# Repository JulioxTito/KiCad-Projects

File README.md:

# KiCad Hardware & PCB Design Portfolio
**Julio Tito** | Electrical & Computer Engineering (ECE)  
[GitHub Profile](https://github.com/JulioxTito) • [Master Portfolio & Interview Packet (PDF)](docs/Julio_Tito_Complete_Hardware_Portfolio_Master.pdf) • [Engineering Defense Guide](docs/Interview_Defense_Guide.pdf)

---

## 📌 Overview
This repository serves as a centralized hardware engineering portfolio demonstrating custom Printed Circuit Board (PCB) designs created in **KiCad**. The projects span fundamental analog signal generation, embedded microcontroller robotics systems, and complex 4-layer high-speed digital carrier boards featuring controlled-impedance differential signaling.

Each project showcases both the **3D Raytraced Hardware Model** and the **2D KiCad PCB Designer Layout**, accompanied by production Gerbers, schematics, and design calculations.

---

## 🚀 Featured Hardware Projects

### 1. [Raspberry Pi CM4 High-Speed Carrier Board](01_CM4_HighSpeed_Carrier/)
> **4-Layer High-Speed Digital Carrier** | Broadcom BCM2711, PCIe Gen 2 ($5\text{ Gbps}$) NVMe SSD, Gigabit Ethernet, 4K HDMI, Dual USB 2.0

<p align="center">
  <em>(Left) 3D Raytraced assembly with M.2 NVMe SSD, RJ45 MagJack, and HDMI. (Right) KiCad PCB Editor routing and floorplan.</em>
</p>

* **Stackup**: JLCPCB JLC04161H-7628 ($1.6\text{ mm}$, FR-4 $\epsilon_r \approx 4.6$) with unbroken Layer 2 Ground plane.
* **Controlled Impedance**: PCIe Gen 2 ($100\,\Omega \pm 10\%$, $W=0.20\text{ mm}$, $S=0.18\text{ mm}$) and USB 2.0 ($90\,\Omega \pm 10\%$, $W=0.30\text{ mm}$, $S=0.18\text{ mm}$).
* **Deliverables**: [Project README](01_CM4_HighSpeed_Carrier/) • [Schematics PDF](01_CM4_HighSpeed_Carrier/images/CM4_Schematics.pdf) • [PCB Layout Artwork](01_CM4_HighSpeed_Carrier/images/CM4_PCB_Layout.pdf)

---

### 2. [ESP32-S3 Micromouse Robotics Controller](02_ESP32_Micromouse_Controller/)
> **2-Layer Autonomous Robotics Motherboard** | ESP32-S3 Dual-Core MCU, Dual H-Bridge Motor Drivers, Optical Encoders, IR Sensors

<p align="center">
  <em>(Left) Full-board raytraced 3D isometric perspective. (Right) KiCad PCB Editor layout with ground plane flood.</em>
</p>

* **Core Subsystem**: ESP32-S3-WROOM-1 (240 MHz dual-core Xtensa LX7, Wi-Fi / BLE) with RF antenna keep-out.
* **Peripherals**: Dual H-bridge motor drivers, optical quadrature encoder inputs for closed-loop PID control, dual ToF/IR sensor headers, onboard DC-DC buck power delivery.
* **Deliverables**: [Project README](02_ESP32_Micromouse_Controller/) • [Schematics PDF](02_ESP32_Micromouse_Controller/images/ESP32_Micromouse_Schematic.pdf) • [PCB Layout Artwork](02_ESP32_Micromouse_Controller/images/ESP32_Micromouse_PCB_Layout.pdf)

---

### 3. [LM555 Precision Timer Testboard](03_LM555_Timer_Testboard/)
> **2-Layer Analog & Mixed-Signal Platform** | LM555 Precision Timer, Astable Multivibrator, BJT LED Buffers, Test Points

<p align="center">
  <em>(Left) Raytraced 3D model with floor reflections. (Right) KiCad PCB Editor copper routing & silkscreen.</em>
</p>

* **Circuit Physics**: Astable oscillator with frequency $f = \frac{1.44}{(R_1 + 2R_2)C}$ and low-ESR bypass decoupling.
* **Validation Interface**: High-impedance oscilloscope test points (TRIG, THRES, OUT, VCC, GND) for transient & ripple analysis.
* **Deliverables**: [Project README](03_LM555_Timer_Testboard/) • [Schematics PDF](03_LM555_Timer_Testboard/images/LM555_Timer_Schematic.pdf) • [PCB Layout Artwork](03_LM555_Timer_Testboard/images/LM555_Timer_PCB_Layout.pdf)

---

## 📑 Master Portfolio & Review Deliverables

A compiled 25-page hardware portfolio print packet is available in the [`docs/`](docs/) directory:
* 📄 **[Julio_Tito_Complete_Hardware_Portfolio_Master.pdf](docs/Julio_Tito_Complete_Hardware_Portfolio_Master.pdf)**: Complete 25-page unified master packet containing all schematics, 2D PCB artwork, 3D orthographic renders, and stackup calculations.
* 📄 **[Interview_Defense_Guide.pdf](docs/Interview_Defense_Guide.pdf)**: 1-hour interview walkthrough guide covering architecture trade-offs, IPC-2141 impedance math, PDN decoupling, and DRC verification.

---

## 🛠️ Repository Architecture & Future Expansion

This repository is built modularly so small utility boards, breakout shields, and future complex designs can be dropped in easily:

```text
KiCad-Projects/
├── docs/                                    # Master portfolio PDFs and engineering notes
├── 01_CM4_HighSpeed_Carrier/                # 4-layer high-speed PCIe Gen 2 carrier
│   ├── hardware/                            # KiCad .kicad_pro, .kicad_sch, .kicad_pcb
│   ├── images/                              # 3D renders, PCB layout views, schematics
│   └── README.md                            # High-speed routing rules, stackup, power budget
├── 02_ESP32_Micromouse_Controller/          # Dual H-bridge robotics controller
│   ├── hardware/                            # KiCad files, BOM, production Gerbers
│   ├── images/                              # 3D renders, PCB layout views, schematics
│   └── README.md                            # Motor driver isolation, encoder pinouts
├── 03_LM555_Timer_Testboard/                # Analog precision timing circuit
│   ├── hardware/                            # KiCad files, manufacturing outputs
│   ├── images/                              # 3D renders, PCB layout views, schematics
│   └── README.md                            # Multivibrator formulas, test procedures
└── .gitignore                               # Standard KiCad backup and lock file exclusions
```

---
*Created and maintained by Julio Tito (2026).*

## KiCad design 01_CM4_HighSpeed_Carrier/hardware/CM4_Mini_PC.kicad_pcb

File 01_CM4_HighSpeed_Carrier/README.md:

# Raspberry Pi CM4 High-Speed Carrier Board

<p align="center">
  <em>Figure 1: (Left) High-resolution raytraced 3D render showing M.2 NVMe SSD, RJ45 MagJack, HDMI, and dual Hirose DF40 connectors. (Right) KiCad PCB Editor layout showing component clusters and high-speed routing.</em>
</p>

### 📸 Multi-Angle 3D Hardware Perspectives

<p align="center">
  <em>Figure 2: (Left) Rear isometric perspective showing HDMI port, dual USB ports, and real-time clock. (Right) Low-angle perspective profile highlighting connector stack heights and clearance.</em>
</p>

<p align="center">
  <em>Figure 3: (Left) Orthogonal top assembly layout. (Right) Bottom ground plane flood and power plane distributions.</em>
</p>

---

## 📌 Project Summary
A custom 4-layer carrier board designed for the **Raspberry Pi Compute Module 4 (CM4)**. Engineered for high-speed edge computing, this board integrates a high-performance M.2 NVMe SSD over PCIe Gen 2, Gigabit Ethernet, 4K HDMI display output, dual USB 2.0 ports, a real-time clock (RTC), and a 40-pin GPIO expansion interface.

---

## 📐 Key Specifications
* **Host Processor**: Raspberry Pi Compute Module 4 (Broadcom BCM2711 quad-core Cortex-A72) via dual 100-pin Hirose DF40 high-density connectors.
* **Storage Interface**: M.2 Key-M socket supporting PCIe Gen 2 x1 ($5\text{ Gbps}$) NVMe Solid-State Drives.
* **Networking**: 1000BASE-T Gigabit Ethernet via integrated magnetic RJ45 jack.
* **Display Output**: Full-size HDMI 2.0 connector with integrated ESD protection.
* **Peripherals**: 2x USB 2.0 Type-A ports via onboard USB 2.0 hub; Micro-SD slot for CM4 Lite; RTC battery backup.
* **Board Dimensions**: $85\text{ mm} \times 56\text{ mm}$ (compact credit-card form factor).
* **Layer Count**: 4 Layers (Signal – Ground Reference – Power Split – Signal).

---

## ⚡ High-Speed Controlled Impedance & Stackup
Designed against the **JLCPCB JLC04161H-7628** stackup ($1.6\text{ mm}$ total thickness, FR-4 $\epsilon_r \approx 4.6$):

| Layer | Type | Copper Thickness | Dielectric / Prepreg | Nominal Dielectric Thickness |
| :--- | :--- | :---: | :--- | :---: |
| **Layer 1 (Top)** | High-Speed Signals & Local Power | $35\,\mu\text{m}$ ($1\text{ oz}$) | Prepreg 7628 | $0.21\text{ mm}$ ($8.27\text{ mils}$) |
| **Layer 2 (In1)** | **Unbroken Solid Ground Plane (GND)** | $17.5\,\mu\text{m}$ ($0.5\text{ oz}$) | FR-4 Core | $1.065\text{ mm}$ |
| **Layer 3 (In2)** | **Power Distribution Planes (+3.3V, +5V, +12V)** | $17.5\,\mu\text{m}$ ($0.5\text{ oz}$) | Prepreg 7628 | $0.21\text{ mm}$ ($8.27\text{ mils}$) |
| **Layer 4 (Bottom)**| High-Speed Signals & Low-Speed I/O | $35\,\mu\text{m}$ ($1\text{ oz}$) | — | — |

### Differential Pair Constraints
* **PCIe Gen 2 Differential Pairs** (`PCIE_TX_P/N`, `PCIE_RX_P/N`, `PCIE_CLK_P/N`):
  * Target Differential Impedance: $100\,\Omega \pm 10\%$
  * Trace Width ($W$): $0.20\text{ mm}$ | Gap ($S$): $0.18\text{ mm}$ | Intra-pair Length Mismatch: $<0.15\text{ mm}$ ($6\text{ mils}$)
* **USB 2.0 High-Speed Pairs** (`USB_D_P/N`):
  * Target Differential Impedance: $90\,\Omega \pm 10\%$
  * Trace Width ($W$): $0.30\text{ mm}$ | Gap ($S$): $0.18\text{ mm}$ | Intra-pair Length Mismatch: $<0.50\text{ mm}$

---

## 📁 Project Directory Contents
* [`hardware/`](hardware/): Complete KiCad project database (`CM4_Mini_PC.kicad_pro`), hierarchical schematics, and PCB layout (`CM4_Mini_PC.kicad_pcb`).
* [`images/cm4_3d_render.png`](images/cm4_3d_render.png): High-resolution raytraced 3D rendering.
* [`images/cm4_pcb_layout.jpg`](images/cm4_pcb_layout.jpg): KiCad PCB Editor layout and floorplan screenshot.
* [`images/CM4_PCB_Layout.pdf`](images/CM4_PCB_Layout.pdf): Vector 2D layout artwork showing copper layers and silk.
* [`images/CM4_Schematics.pdf`](images/CM4_Schematics.pdf): 7-sheet hierarchical schematic packet.

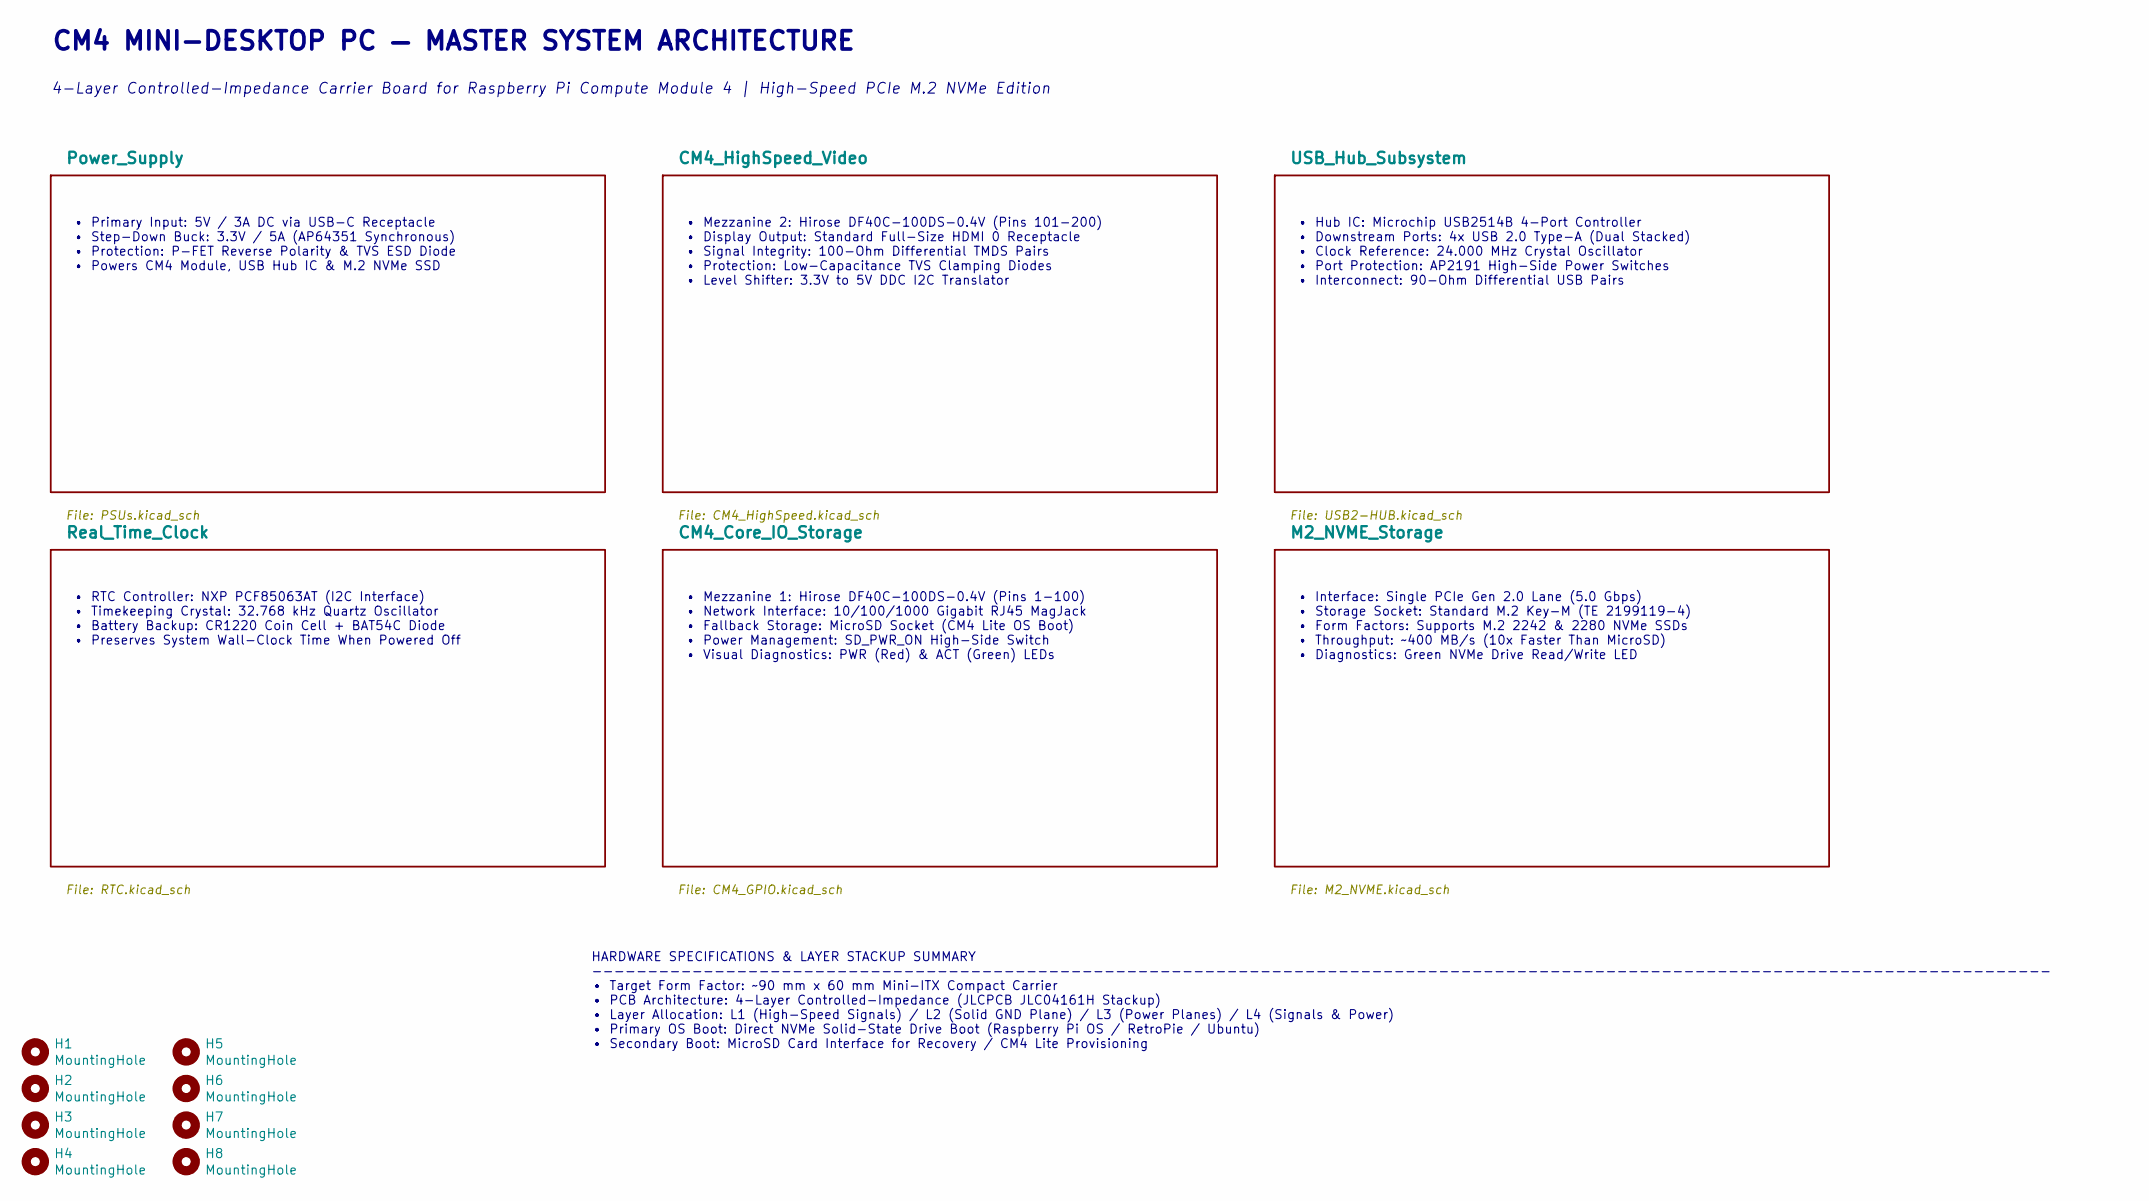
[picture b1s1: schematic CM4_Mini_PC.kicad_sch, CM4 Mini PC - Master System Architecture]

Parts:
H1, H2, H3, H4, H5, H6, H7, H8: MountingHole; MountingHole_2.7mm_M2.5; Part Description M2.5 mounting hole

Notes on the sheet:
CM4 MINI-DESKTOP PC — MASTER SYSTEM ARCHITECTURE
4-Layer Controlled-Impedance Carrier Board for Raspberry Pi Compute Module 4 | High-Speed PCIe M.2 NVMe Edition
• Primary Input: 5V / 3A DC via USB-C Receptacle • Step-Down Buck: 3.3V / 5A (AP64351 Synchronous) • Protection: P-FET Reverse Polarity & TVS ESD Diode • Powers CM4 Module, USB Hub IC & M.2 NVMe SSD
• Mezzanine 2: Hirose DF40C-100DS-0.4V (Pins 101-200) • Display Output: Standard Full-Size HDMI 0 Receptacle • Signal Integrity: 100-Ohm Differential TMDS Pairs • Protection: Low-Capacitance TVS Clamping Diodes • Level Shifter: 3.3V to 5V DDC I2C Translator
• Hub IC: Microchip USB2514B 4-Port Controller • Downstream Ports: 4x USB 2.0 Type-A (Dual Stacked) • Clock Reference: 24.000 MHz Crystal Oscillator • Port Protection: AP2191 High-Side Power Switches • Interconnect: 90-Ohm Differential USB Pairs
• RTC Controller: NXP PCF85063AT (I2C Interface) • Timekeeping Crystal: 32.768 kHz Quartz Oscillator • Battery Backup: CR1220 Coin Cell + BAT54C Diode • Preserves System Wall-Clock Time When Powered Off
• Mezzanine 1: Hirose DF40C-100DS-0.4V (Pins 1-100) • Network Interface: 10/100/1000 Gigabit RJ45 MagJack • Fallback Storage: MicroSD Socket (CM4 Lite OS Boot) • Power Management: SD_PWR_ON High-Side Switch • Visual Diagnostics: PWR (Red) & ACT (Green) LEDs
• Interface: Single PCIe Gen 2.0 Lane (5.0 Gbps) • Storage Socket: Standard M.2 Key-M (TE 2199119-4) • Form Factors: Supports M.2 2242 & 2280 NVMe SSDs • Throughput: ~400 MB/s (10x Faster Than MicroSD) • Diagnostics: Green NVMe Drive Read/Write LED
HARDWARE SPECIFICATIONS & LAYER STACKUP SUMMARY ----------------------------------------------------------------------------------------------------------------------------------- • Target Form Factor: ~90 mm x 60 mm Mini-ITX Compact Carrier • PCB Architecture: 4-Layer Controlled-Impedance (JLCPCB 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

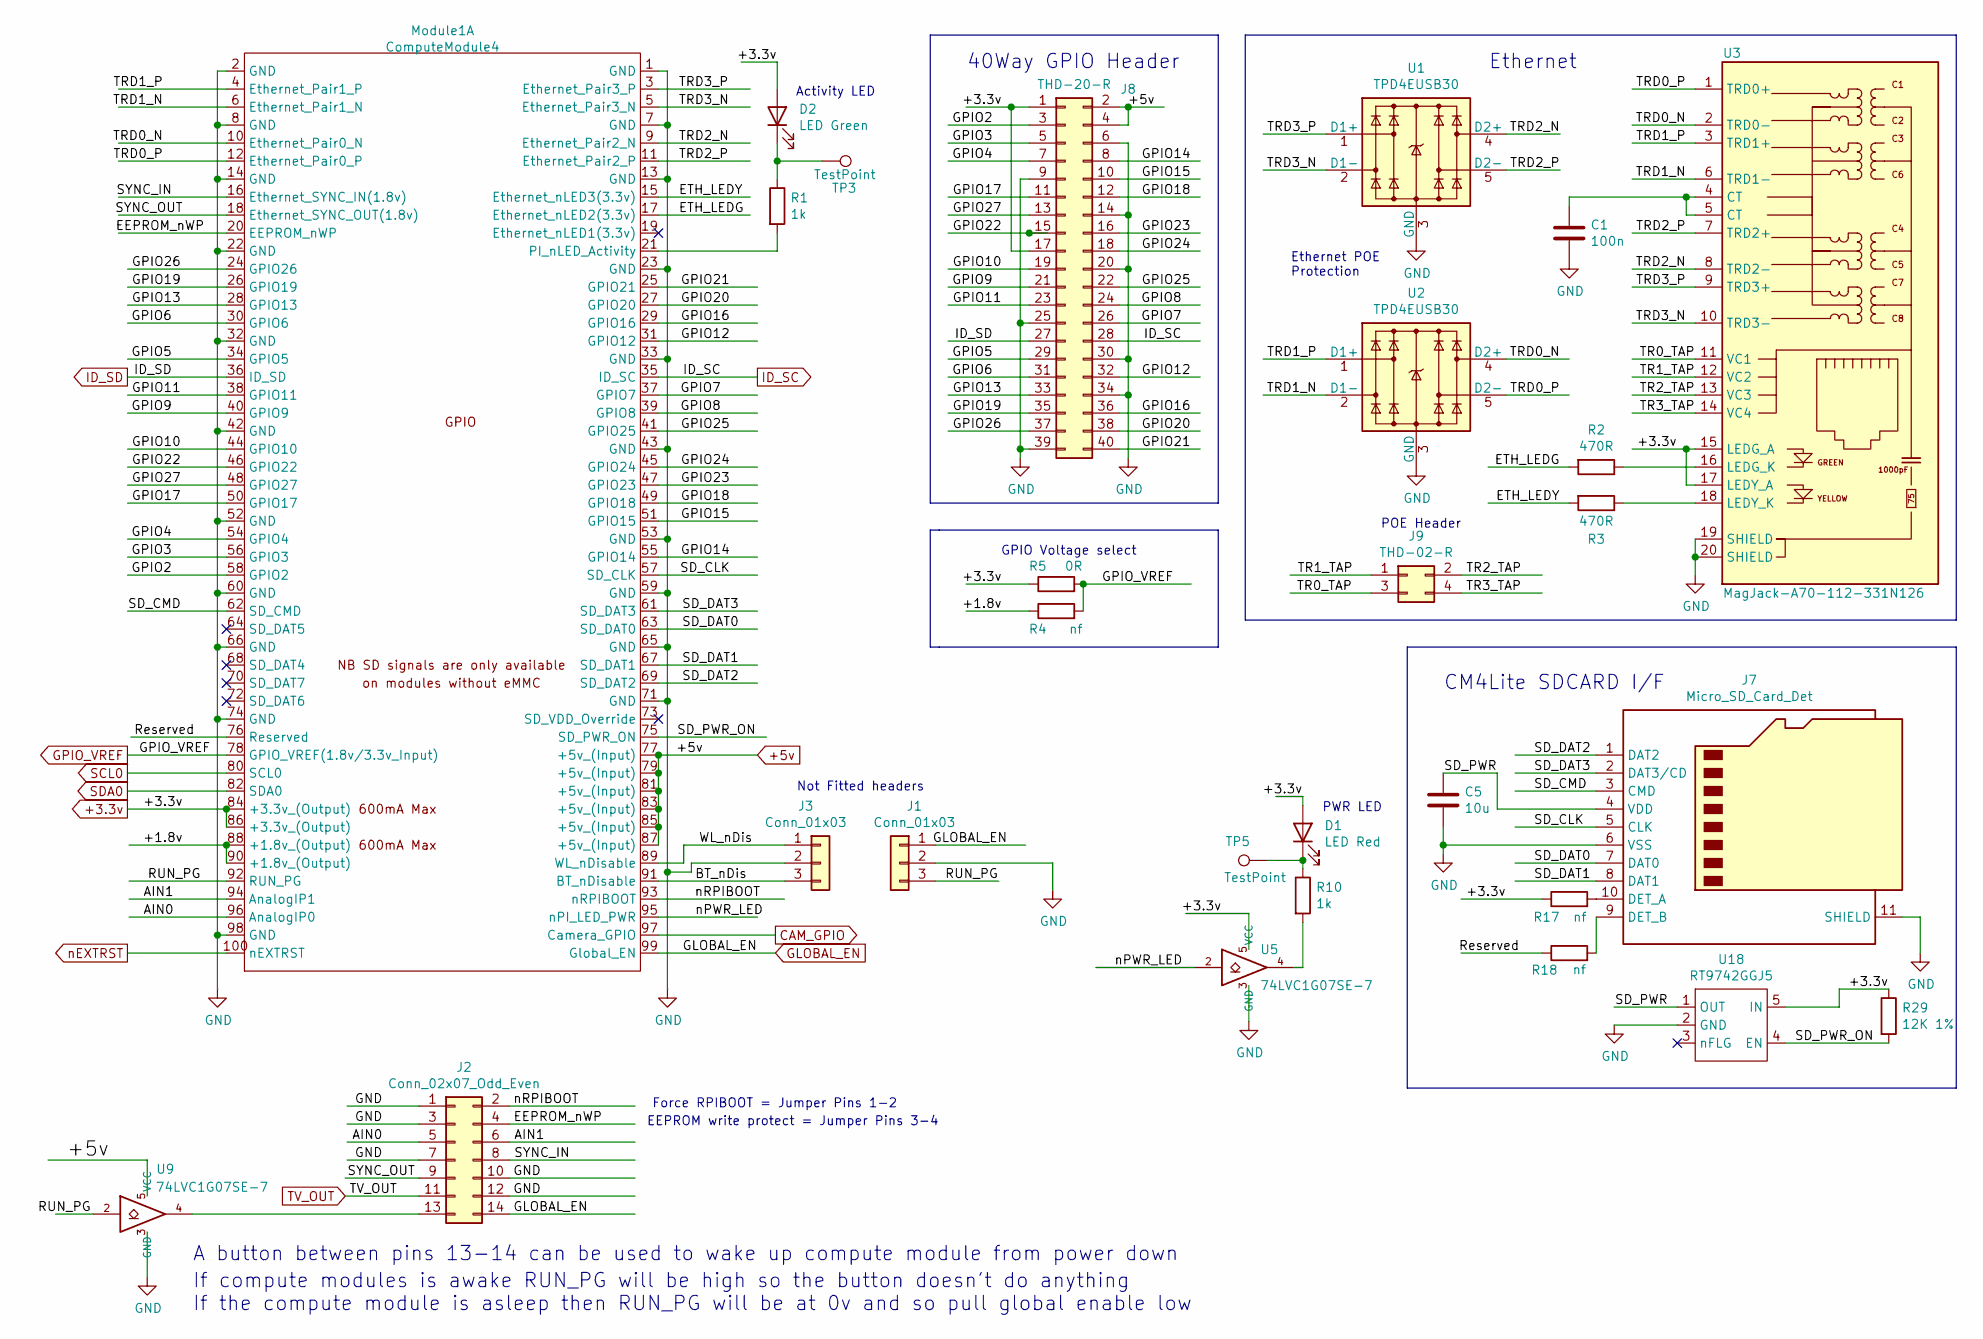
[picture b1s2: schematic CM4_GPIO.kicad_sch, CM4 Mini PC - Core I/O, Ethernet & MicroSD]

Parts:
C1: 100n; C_0402_1005Metric; Part Description 0.1uF 10% 16V Ceramic Capacitor X7R 040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
C5: 10u; C_0805_2012Metric; Part Description 10uF 10% 10V Ceramic Capacitor X7R 0805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
D1: LED Red; LED_0603_1608Metric; Part Description Red 620nm LED Indication - Discrete 2.2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
D2: LED Green; LED_0603_1608Metric; Part Description Green 572nm LED Indication - Discrete 2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
J1, J3: Conn_01x03; PinHeader_1x03_P2.54mm_Vertical; Part Description 3pin 0.1" connector
J2: Conn_02x07_Odd_Even; PinHeader_2x07_P2.54mm_Vertical; Part Description PinHeader_2x07_P2.54mm_Vertical
J7: Micro_SD_Card_Det; SDCARD_MOLEX_503398-1892; Part Description 9 (8 + 1) Position Card Connector micro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
J8: THD-20-R; PinHeader_2x20_P2.54mm_Vertical; Part Description PinHeader_2x20_P2.54mm_Vertical
J9: THD-02-R; PinHeader_2x02_P2.54mm_Vertical; Part Description PinHeader_2x02_P2.54mm_Vertical
Module1: ComputeModule4; Raspberry-Pi-4-Compute-Module; Part Description 100 Position Connector Receptacle, Cent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
R1, R10: 1k; R_0402_1005Metric; Part Description Resistor 1K M1005 1% 63mW
R2, R3: 470R; R_0402_1005Metric; Part Description Resistor 470R M1005 1% 63mW
R4: nf; R_0805_2012Metric_Pad1.20x1.40mm_HandSolder
R5: 0R; R_0805_2012Metric_Pad1.20x1.40mm_HandSolder; Part Description Resistor 0R M2012 5%
R17, R18: nf; R_0402_1005Metric; Part Description Resistor 1K M1005 1% 63mW
R29: 12K 1%; R_0402_1005Metric; Part Description Resistor 12K M1005 1% 63mW
TP3, TP5: TestPoint; TestPoint_Pad_2.0x2.0mm
U1, U2: TPD4EUSB30; USON-10_2.5x1.0mm_P0.5mm; Part Description Quad TVS diode for high speed signals (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
U3: MagJack-A70-112-331N126; TRJG0926HENL; Part Description Gigabit Ethernet Magjack
U5, U9: 74LVC1G07SE-7; SOT-353_SC-70-5; Part Description Buffer, Non-Inverting 1 Element 1 Bit p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
U18: RT9742GGJ5; SOT-23-5; Part Description Power Switch/Driver 1:1 N-Channel 1A TS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

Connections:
+3.3v: D1.2 (A), D2.2 (A), J8.1, J8.17, Module1.84 (+3.3v_(Output)), Module1.86 (+3.3v_(Output)), R5.1, R17.1, R29.1, U3.15 (LEDG_A), U3.17 (LEDY_A), U5.5 (VCC), U18.5 (IN); also elsewhere on the board
+5v: J8.2, J8.4, Module1.77 (+5v_(Input)), Module1.79 (+5v_(Input)), Module1.81 (+5v_(Input)), Module1.83 (+5v_(Input)), Module1.85 (+5v_(Input)), Module1.87 (+5v_(Input)), U9.5 (VCC); also elsewhere on the board
/CM4_Core_IO_Storage/+1.8v: Module1.88 (+1.8v_(Output)), Module1.90 (+1.8v_(Output)), R4.1
/CM4_Core_IO_Storage/AIN0: J2.5, Module1.96 (AnalogIP0)
/CM4_Core_IO_Storage/AIN1: J2.6, Module1.94 (AnalogIP1)
/CM4_Core_IO_Storage/BT_nDis: J3.3, Module1.91 (BT_nDisable)
/CM4_Core_IO_Storage/EEPROM_nWP: J2.4, Module1.20 (EEPROM_nWP)
/CM4_Core_IO_Storage/ETH_LEDG: Module1.17 (Ethernet_nLED2(3.3v)), R2.2
/CM4_Core_IO_Storage/ETH_LEDY: Module1.15 (Ethernet_nLED3(3.3v)), R3.2
/CM4_Core_IO_Storage/GPIO2: J8.3, Module1.58 (GPIO2)
/CM4_Core_IO_Storage/GPIO3: J8.5, Module1.56 (GPIO3)
/CM4_Core_IO_Storage/GPIO4: J8.7, Module1.54 (GPIO4)
/CM4_Core_IO_Storage/GPIO5: J8.29, Module1.34 (GPIO5)
/CM4_Core_IO_Storage/GPIO6: J8.31, Module1.30 (GPIO6)
/CM4_Core_IO_Storage/GPIO7: J8.26, Module1.37 (GPIO7)
/CM4_Core_IO_Storage/GPIO8: J8.24, Module1.39 (GPIO8)
/CM4_Core_IO_Storage/GPIO9: J8.21, Module1.40 (GPIO9)
/CM4_Core_IO_Storage/GPIO10: J8.19, Module1.44 (GPIO10)
/CM4_Core_IO_Storage/GPIO11: J8.23, Module1.38 (GPIO11)
/CM4_Core_IO_Storage/GPIO12: J8.32, Module1.31 (GPIO12)
/CM4_Core_IO_Storage/GPIO13: J8.33, Module1.28 (GPIO13)
/CM4_Core_IO_Storage/GPIO14: J8.8, Module1.55 (GPIO14)
/CM4_Core_IO_Storage/GPIO15: J8.10, Module1.51 (GPIO15)
/CM4_Core_IO_Storage/GPIO16: J8.36, Module1.29 (GPIO16)
/CM4_Core_IO_Storage/GPIO17: J8.11, Module1.50 (GPIO17)
/CM4_Core_IO_Storage/GPIO18: J8.12, Module1.49 (GPIO18)
/CM4_Core_IO_Storage/GPIO19: J8.35, Module1.26 (GPIO19)
/CM4_Core_IO_Storage/GPIO20: J8.38, Module1.27 (GPIO20)
/CM4_Core_IO_Storage/GPIO21: J8.40, Module1.25 (GPIO21)
/CM4_Core_IO_Storage/GPIO22: J8.15, Module1.46 (GPIO22)
/CM4_Core_IO_Storage/GPIO23: J8.16, Module1.47 (GPIO23)
/CM4_Core_IO_Storage/GPIO24: J8.18, Module1.45 (GPIO24)
/CM4_Core_IO_Storage/GPIO25: J8.22, Module1.41 (GPIO25)
/CM4_Core_IO_Storage/GPIO26: J8.37, Module1.24 (GPIO26)
/CM4_Core_IO_Storage/GPIO27: J8.13, Module1.48 (GPIO27)
/CM4_Core_IO_Storage/RUN_PG: J1.3, Module1.92 (RUN_PG), U9.2
/CM4_Core_IO_Storage/Reserved: Module1.76 (Reserved), R18.1
/CM4_Core_IO_Storage/SD_CLK: J7.5 (CLK), Module1.57 (SD_CLK)
/CM4_Core_IO_Storage/SD_CMD: J7.3 (CMD), Module1.62 (SD_CMD)
/CM4_Core_IO_Storage/SD_DAT0: J7.7 (DAT0), Module1.63 (SD_DAT0)
/CM4_Core_IO_Storage/SD_DAT1: J7.8 (DAT1), Module1.67 (SD_DAT1)
/CM4_Core_IO_Storage/SD_DAT2: J7.1 (DAT2), Module1.69 (SD_DAT2)
/CM4_Core_IO_Storage/SD_DAT3: J7.2 (DAT3/CD), Module1.61 (SD_DAT3)
/CM4_Core_IO_Storage/SD_PWR: C5.1, J7.4 (VDD), U18.1 (OUT)
/CM4_Core_IO_Storage/SD_PWR_ON: Module1.75 (SD_PWR_ON), R29.2, U18.4 (EN)
/CM4_Core_IO_Storage/SYNC_IN: J2.8, Module1.16 (Ethernet_SYNC_IN(1.8v))
/CM4_Core_IO_Storage/SYNC_OUT: J2.9, Module1.18 (Ethernet_SYNC_OUT(1.8v))
/CM4_Core_IO_Storage/TR0_TAP: J9.3, U3.11 (VC1)
/CM4_Core_IO_Storage/TR1_TAP: J9.1, U3.12 (VC2)
/CM4_Core_IO_Storage/TR2_TAP: J9.2, U3.13 (VC3)
/CM4_Core_IO_Storage/TR3_TAP: J9.4, U3.14 (VC4)
/CM4_Core_IO_Storage/TRD0_N: Module1.10 (Ethernet_Pair0_N), U2.4 (D2+), U2.7, U3.2 (TRD0-)
/CM4_Core_IO_Storage/TRD0_P: Module1.12 (Ethernet_Pair0_P), U2.5 (D2-), U2.6, U3.1 (TRD0+)
/CM4_Core_IO_Storage/TRD1_N: Module1.6 (Ethernet_Pair1_N), U2.2 (D1-), U2.9, U3.6 (TRD1-)
/CM4_Core_IO_Storage/TRD1_P: Module1.4 (Ethernet_Pair1_P), U2.1 (D1+), U2.10, U3.3 (TRD1+)
/CM4_Core_IO_Storage/TRD2_N: Module1.9 (Ethernet_Pair2_N), U1.4 (D2+), U1.7, U3.8 (TRD2-)
/CM4_Core_IO_Storage/TRD2_P: Module1.11 (Ethernet_Pair2_P), U1.5 (D2-), U1.6, U3.7 (TRD2+)
/CM4_Core_IO_Storage/TRD3_N: Module1.5 (Ethernet_Pair3_N), U1.2 (D1-), U1.9, U3.10 (TRD3-)
/CM4_Core_IO_Storage/TRD3_P: Module1.3 (Ethernet_Pair3_P), U1.1 (D1+), U1.10, U3.9 (TRD3+)
/CM4_Core_IO_Storage/WL_nDis: J3.1, Module1.89 (WL_nDisable)
/CM4_Core_IO_Storage/nPWR_LED: Module1.95 (nPI_LED_PWR), U5.2
/CM4_Core_IO_Storage/nRPIBOOT: J2.2, Module1.93 (nRPIBOOT)
CAM_GPIO: Module1.97 (Camera_GPIO); also elsewhere on the board
GLOBAL_EN: J1.1, J2.14, Module1.99 (Global_EN); also elsewhere on the board
GND: C1.2, C5.2, J1.2, J2.1, J2.3, J2.7, J2.10, J2.12, J3.2, J7.6 (VSS), J7.11 (SHIELD), J8.6, J8.9, J8.14, J8.20, J8.25, J8.30, J8.34, J8.39, Module1.1 (GND), Module1.2 (GND), Module1.7 (GND), Module1.8 (GND), Module1.13 (GND), Module1.14 (GND), Module1.22 (GND), Module1.23 (GND), Module1.32 (GND), Module1.33 (GND), Module1.42 (GND), Module1.43 (GND), Module1.52 (GND), Module1.53 (GND), Module1.59 (GND), Module1.60 (GND), Module1.65 (GND), Module1.66 (GND), Module1.71 (GND), Module1.74 (GND), Module1.98 (GND), U1.3 (GND), U1.8 (GND), U2.3 (GND), U2.8 (GND), U3.19 (SHIELD), U3.20 (SHIELD), U5.3 (GND), U9.3 (GND), U18.2 (GND); also elsewhere on the board
GPIO_VREF: Module1.78 (GPIO_VREF(1.8v/3.3v_Input)), R4.2, R5.2; also elsewhere on the board
ID_SC: J8.28, Module1.35 (ID_SC)
ID_SD: J8.27, Module1.36 (ID_SD)
unnamed: C1.1, U3.4 (CT), U3.5 (CT)
unnamed: D1.1 (K), R10.1, TP5.1 (1_1)
unnamed: D2.1 (K), R1.1, TP3.1 (1_1)
unnamed: J2.13, U9.4
unnamed: J7.10 (DET_A), R17.2
unnamed: J7.9 (DET_B), R18.2
unnamed: Module1.21 (PI_nLED_Activity), R1.2
unnamed: R10.2, U5.4
unnamed: R2.1, U3.16 (LEDG_K)
unnamed: R3.1, U3.18 (LEDY_K)
SCL0: Module1.80 (SCL0); also elsewhere on the board
SDA0: Module1.82 (SDA0); also elsewhere on the board
TV_OUT: J2.11; also elsewhere on the board
nEXTRST: Module1.100 (nEXTRST); also elsewhere on the board

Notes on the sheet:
PWR LED
Ethernet POE Protection
40Way GPIO Header
CM4Lite SDCARD I/F
GPIO Voltage select
Ethernet
Activity LED
EEPROM write protect = Jumper Pins 3-4
Not Fitted headers
A button between pins 13-14 can be used to wake up compute module from power down
If compute modules is awake RUN_PG will be high so the button doesn't do anything If the compute module is asleep then RUN_PG will be at 0v and so pull global enable low
Force RPIBOOT = Jumper Pins 1-2
POE Header

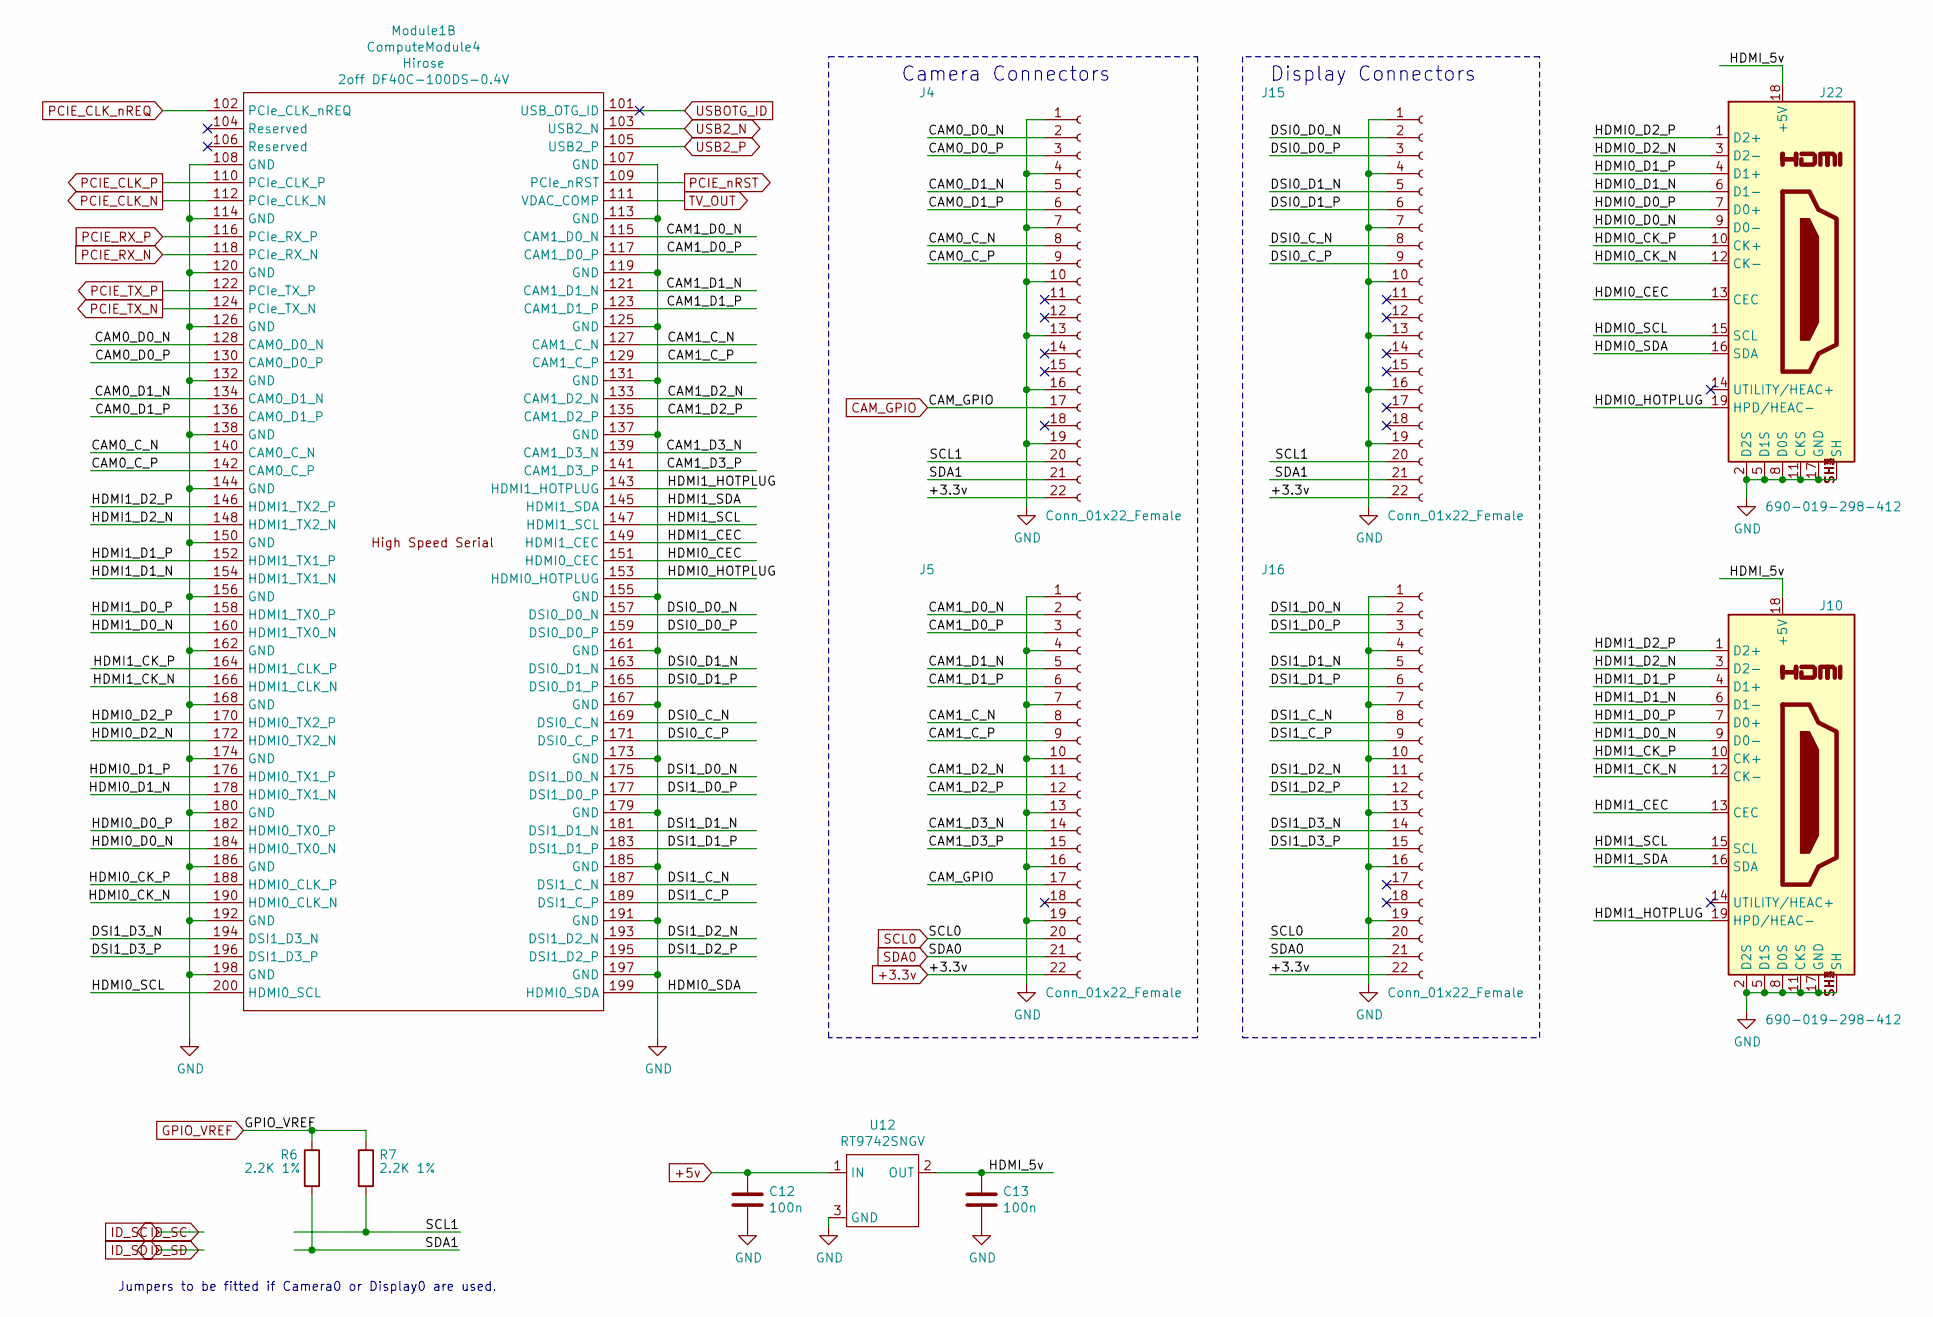
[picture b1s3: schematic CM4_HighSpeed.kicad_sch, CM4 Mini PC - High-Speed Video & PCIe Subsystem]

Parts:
C12, C13: 100n; C_0402_1005Metric; Part Description 0.1uF 10% 16V Ceramic Capacitor X7R 040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
J4, J5, J15, J16: Conn_01x22_Female; Hirose_FH12-22S-0.5SH_1x22-1MP_P0.50mm_Horizontal; Part Description 22 Position FFC, FPC Connector Contacts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
J10, J22: 690-019-298-412; EDAC 690-019-298-412; Part Description HDMI Connector, Right Angle, 19 Contact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
Module1: ComputeModule4; Raspberry-Pi-4-Compute-Module; Part Description 100 Position Connector Receptacle, Cent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
R6, R7: 2.2K 1%; R_0402_1005Metric; Part Description Resistor 2.2K M1005 1% 63mW
U12: RT9742SNGV; SOT-23; Part Description Power Switch/Driver 1:1 N-Channel 500mA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

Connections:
+3.3v: J4.22, J5.22, J15.22, J16.22; also elsewhere on the board
+5v: C12.1, U12.1 (IN); also elsewhere on the board
/CM4_HighSpeed_Video/CAM0_C_N: J4.8, Module1.140 (CAM0_C_N)
/CM4_HighSpeed_Video/CAM0_C_P: J4.9, Module1.142 (CAM0_C_P)
/CM4_HighSpeed_Video/CAM0_D0_N: J4.2, Module1.128 (CAM0_D0_N)
/CM4_HighSpeed_Video/CAM0_D0_P: J4.3, Module1.130 (CAM0_D0_P)
/CM4_HighSpeed_Video/CAM0_D1_N: J4.5, Module1.134 (CAM0_D1_N)
/CM4_HighSpeed_Video/CAM0_D1_P: J4.6, Module1.136 (CAM0_D1_P)
/CM4_HighSpeed_Video/CAM1_C_N: J5.8, Module1.127 (CAM1_C_N)
/CM4_HighSpeed_Video/CAM1_C_P: J5.9, Module1.129 (CAM1_C_P)
/CM4_HighSpeed_Video/CAM1_D0_N: J5.2, Module1.115 (CAM1_D0_N)
/CM4_HighSpeed_Video/CAM1_D0_P: J5.3, Module1.117 (CAM1_D0_P)
/CM4_HighSpeed_Video/CAM1_D1_N: J5.5, Module1.121 (CAM1_D1_N)
/CM4_HighSpeed_Video/CAM1_D1_P: J5.6, Module1.123 (CAM1_D1_P)
/CM4_HighSpeed_Video/CAM1_D2_N: J5.11, Module1.133 (CAM1_D2_N)
/CM4_HighSpeed_Video/CAM1_D2_P: J5.12, Module1.135 (CAM1_D2_P)
/CM4_HighSpeed_Video/CAM1_D3_N: J5.14, Module1.139 (CAM1_D3_N)
/CM4_HighSpeed_Video/CAM1_D3_P: J5.15, Module1.141 (CAM1_D3_P)
/CM4_HighSpeed_Video/DSI0_C_N: J15.8, Module1.169 (DSI0_C_N)
/CM4_HighSpeed_Video/DSI0_C_P: J15.9, Module1.171 (DSI0_C_P)
/CM4_HighSpeed_Video/DSI0_D0_N: J15.2, Module1.157 (DSI0_D0_N)
/CM4_HighSpeed_Video/DSI0_D0_P: J15.3, Module1.159 (DSI0_D0_P)
/CM4_HighSpeed_Video/DSI0_D1_N: J15.5, Module1.163 (DSI0_D1_N)
/CM4_HighSpeed_Video/DSI0_D1_P: J15.6, Module1.165 (DSI0_D1_P)
/CM4_HighSpeed_Video/DSI1_C_N: J16.8, Module1.187 (DSI1_C_N)
/CM4_HighSpeed_Video/DSI1_C_P: J16.9, Module1.189 (DSI1_C_P)
/CM4_HighSpeed_Video/DSI1_D0_N: J16.2, Module1.175 (DSI1_D0_N)
/CM4_HighSpeed_Video/DSI1_D0_P: J16.3, Module1.177 (DSI1_D0_P)
/CM4_HighSpeed_Video/DSI1_D1_N: J16.5, Module1.181 (DSI1_D1_N)
/CM4_HighSpeed_Video/DSI1_D1_P: J16.6, Module1.183 (DSI1_D1_P)
/CM4_HighSpeed_Video/DSI1_D2_N: J16.11, Module1.193 (DSI1_D2_N)
/CM4_HighSpeed_Video/DSI1_D2_P: J16.12, Module1.195 (DSI1_D2_P)
/CM4_HighSpeed_Video/DSI1_D3_N: J16.14, Module1.194 (DSI1_D3_N)
/CM4_HighSpeed_Video/DSI1_D3_P: J16.15, Module1.196 (DSI1_D3_P)
/CM4_HighSpeed_Video/HDMI0_CEC: J22.13 (CEC), Module1.151 (HDMI0_CEC)
/CM4_HighSpeed_Video/HDMI0_CK_N: J22.12 (CK-), Module1.190 (HDMI0_CLK_N)
/CM4_HighSpeed_Video/HDMI0_CK_P: J22.10 (CK+), Module1.188 (HDMI0_CLK_P)
/CM4_HighSpeed_Video/HDMI0_D0_N: J22.9 (D0-), Module1.184 (HDMI0_TX0_N)
/CM4_HighSpeed_Video/HDMI0_D0_P: J22.7 (D0+), Module1.182 (HDMI0_TX0_P)
/CM4_HighSpeed_Video/HDMI0_D1_N: J22.6 (D1-), Module1.178 (HDMI0_TX1_N)
/CM4_HighSpeed_Video/HDMI0_D1_P: J22.4 (D1+), Module1.176 (HDMI0_TX1_P)
/CM4_HighSpeed_Video/HDMI0_D2_N: J22.3 (D2-), Module1.172 (HDMI0_TX2_N)
/CM4_HighSpeed_Video/HDMI0_D2_P: J22.1 (D2+), Module1.170 (HDMI0_TX2_P)
/CM4_HighSpeed_Video/HDMI0_HOTPLUG: J22.19 (HPD/HEAC-), Module1.153 (HDMI0_HOTPLUG)
/CM4_HighSpeed_Video/HDMI0_SCL: J22.15 (SCL), Module1.200 (HDMI0_SCL)
/CM4_HighSpeed_Video/HDMI0_SDA: J22.16 (SDA), Module1.199 (HDMI0_SDA)
/CM4_HighSpeed_Video/HDMI1_CEC: J10.13 (CEC), Module1.149 (HDMI1_CEC)
/CM4_HighSpeed_Video/HDMI1_CK_N: J10.12 (CK-), Module1.166 (HDMI1_CLK_N)
/CM4_HighSpeed_Video/HDMI1_CK_P: J10.10 (CK+), Module1.164 (HDMI1_CLK_P)
/CM4_HighSpeed_Video/HDMI1_D0_N: J10.9 (D0-), Module1.160 (HDMI1_TX0_N)
/CM4_HighSpeed_Video/HDMI1_D0_P: J10.7 (D0+), Module1.158 (HDMI1_TX0_P)
/CM4_HighSpeed_Video/HDMI1_D1_N: J10.6 (D1-), Module1.154 (HDMI1_TX1_N)
/CM4_HighSpeed_Video/HDMI1_D1_P: J10.4 (D1+), Module1.152 (HDMI1_TX1_P)
/CM4_HighSpeed_Video/HDMI1_D2_N: J10.3 (D2-), Module1.148 (HDMI1_TX2_N)
/CM4_HighSpeed_Video/HDMI1_D2_P: J10.1 (D2+), Module1.146 (HDMI1_TX2_P)
/CM4_HighSpeed_Video/HDMI1_HOTPLUG: J10.19 (HPD/HEAC-), Module1.143 (HDMI1_HOTPLUG)
/CM4_HighSpeed_Video/HDMI1_SCL: J10.15 (SCL), Module1.147 (HDMI1_SCL)
/CM4_HighSpeed_Video/HDMI1_SDA: J10.16 (SDA), Module1.145 (HDMI1_SDA)
/CM4_HighSpeed_Video/HDMI_5v: C13.1, J10.18 (+5V), J22.18 (+5V), U12.2 (OUT)
/CM4_HighSpeed_Video/SCL1: J4.20, J15.20, R7.2
/CM4_HighSpeed_Video/SDA1: J4.21, J15.21, R6.2
CAM_GPIO: J4.17, J5.17; also elsewhere on the board
GND: C12.2, C13.2, J4.1, J4.4, J4.7, J4.10, J4.13, J4.16, J4.19, J5.1, J5.4, J5.7, J5.10, J5.13, J5.16, J5.19, J10.2 (D2S), J10.5 (D1S), J10.8 (D0S), J10.11 (CKS), J10.17 (GND), J10.SH1 (SH), J10.SH2 (SH), J10.SH3 (SH), J10.SH4 (SH), J15.1, J15.4, J15.7, J15.10, J15.13, J15.16, J15.19, J16.1, J16.4, J16.7, J16.10, J16.13, J16.16, J16.19, J22.2 (D2S), J22.5 (D1S), J22.8 (D0S), J22.11 (CKS), J22.17 (GND), J22.SH1 (SH), J22.SH2 (SH), J22.SH3 (SH), J22.SH4 (SH), Module1.107 (GND), Module1.108 (GND), Module1.113 (GND), Module1.114 (GND), Module1.119 (GND), Module1.120 (GND), Module1.125 (GND), Module1.126 (GND), Module1.131 (GND), Module1.132 (GND), Module1.137 (GND), Module1.138 (GND), Module1.144 (GND), Module1.150 (GND), Module1.155 (GND), Module1.156 (GND), Module1.161 (GND), Module1.162 (GND), Module1.167 (GND), Module1.168 (GND), Module1.173 (GND), Module1.174 (GND), Module1.179 (GND), Module1.180 (GND), Module1.185 (GND), Module1.186 (GND), Module1.191 (GND), Module1.192 (GND), Module1.197 (GND), Module1.198 (GND), U12.3 (GND); also elsewhere on the board
GPIO_VREF: R6.1, R7.1; also elsewhere on the board
PCIE_CLK_N: Module1.112 (PCIe_CLK_N); also elsewhere on the board
PCIE_CLK_P: Module1.110 (PCIe_CLK_P); also elsewhere on the board
PCIE_CLK_nREQ: Module1.102 (PCIe_CLK_nREQ); also elsewhere on the board
PCIE_RX_N: Module1.118 (PCIe_RX_N); also elsewhere on the board
PCIE_RX_P: Module1.116 (PCIe_RX_P); also elsewhere on the board
PCIE_TX_N: Module1.124 (PCIe_TX_N); also elsewhere on the board
PCIE_TX_P: Module1.122 (PCIe_TX_P); also elsewhere on the board
PCIE_nRST: Module1.109 (PCIe_nRST); also elsewhere on the board
SCL0: J5.20, J16.20; also elsewhere on the board
SDA0: J5.21, J16.21; also elsewhere on the board
TV_OUT: Module1.111 (VDAC_COMP); also elsewhere on the board
USB2_N: Module1.103 (USB2_N); also elsewhere on the board
USB2_P: Module1.105 (USB2_P); also elsewhere on the board
USBOTG_ID: Module1.101 (USB_OTG_ID)

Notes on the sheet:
Jumpers to be fitted if Camera0 or Display0 are used.
Camera Connectors
Display Connectors
